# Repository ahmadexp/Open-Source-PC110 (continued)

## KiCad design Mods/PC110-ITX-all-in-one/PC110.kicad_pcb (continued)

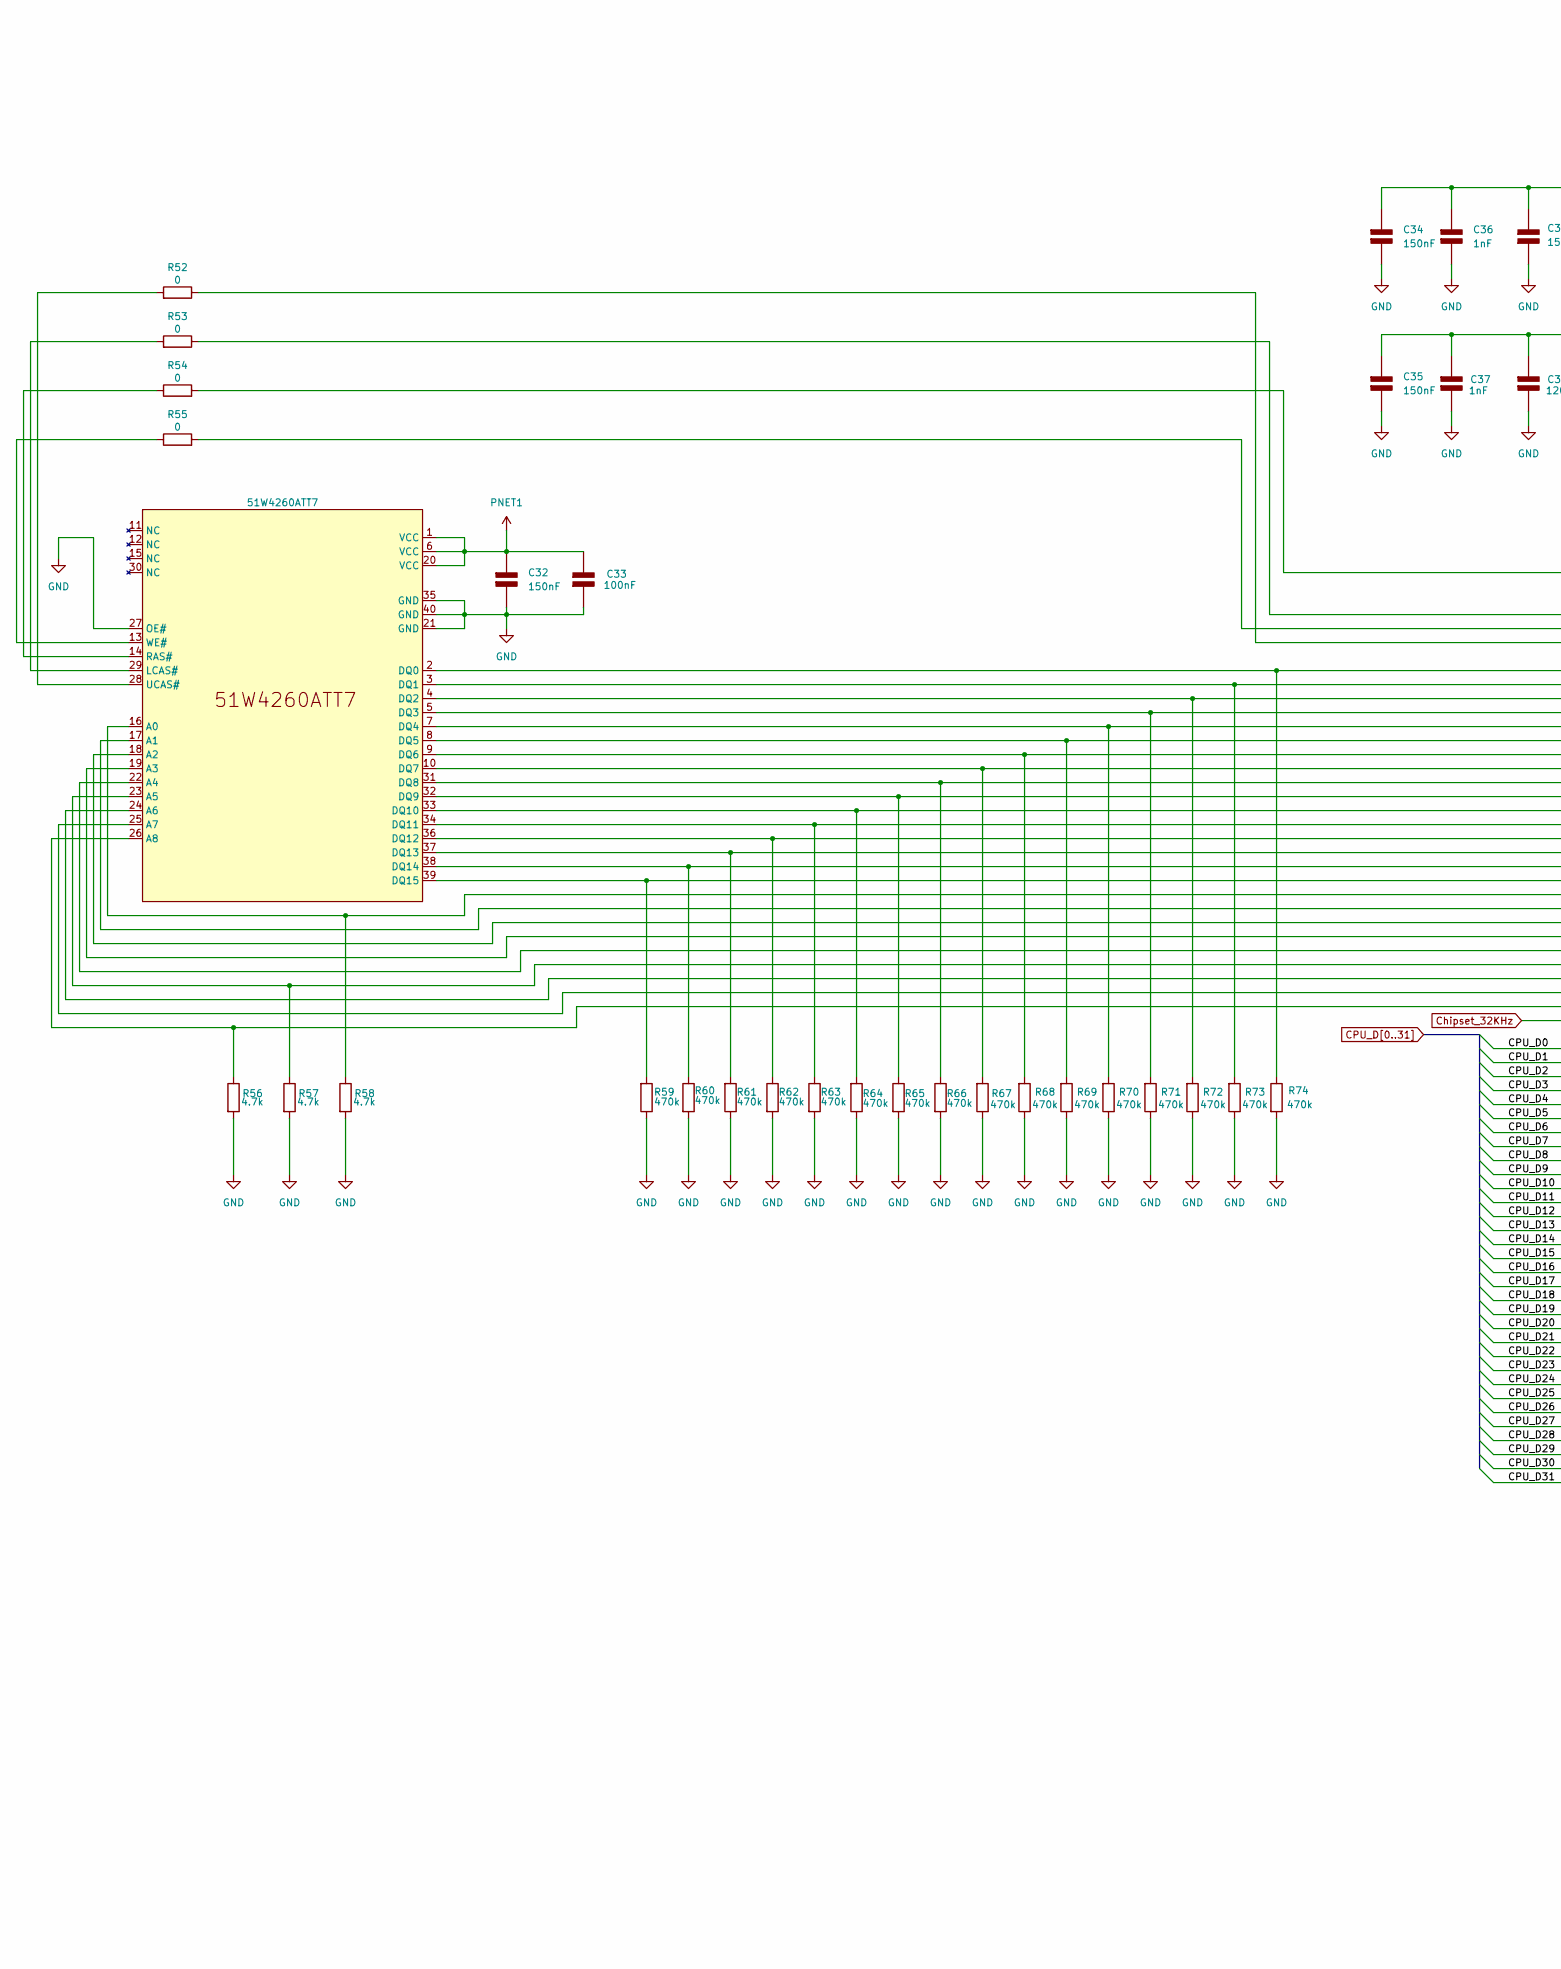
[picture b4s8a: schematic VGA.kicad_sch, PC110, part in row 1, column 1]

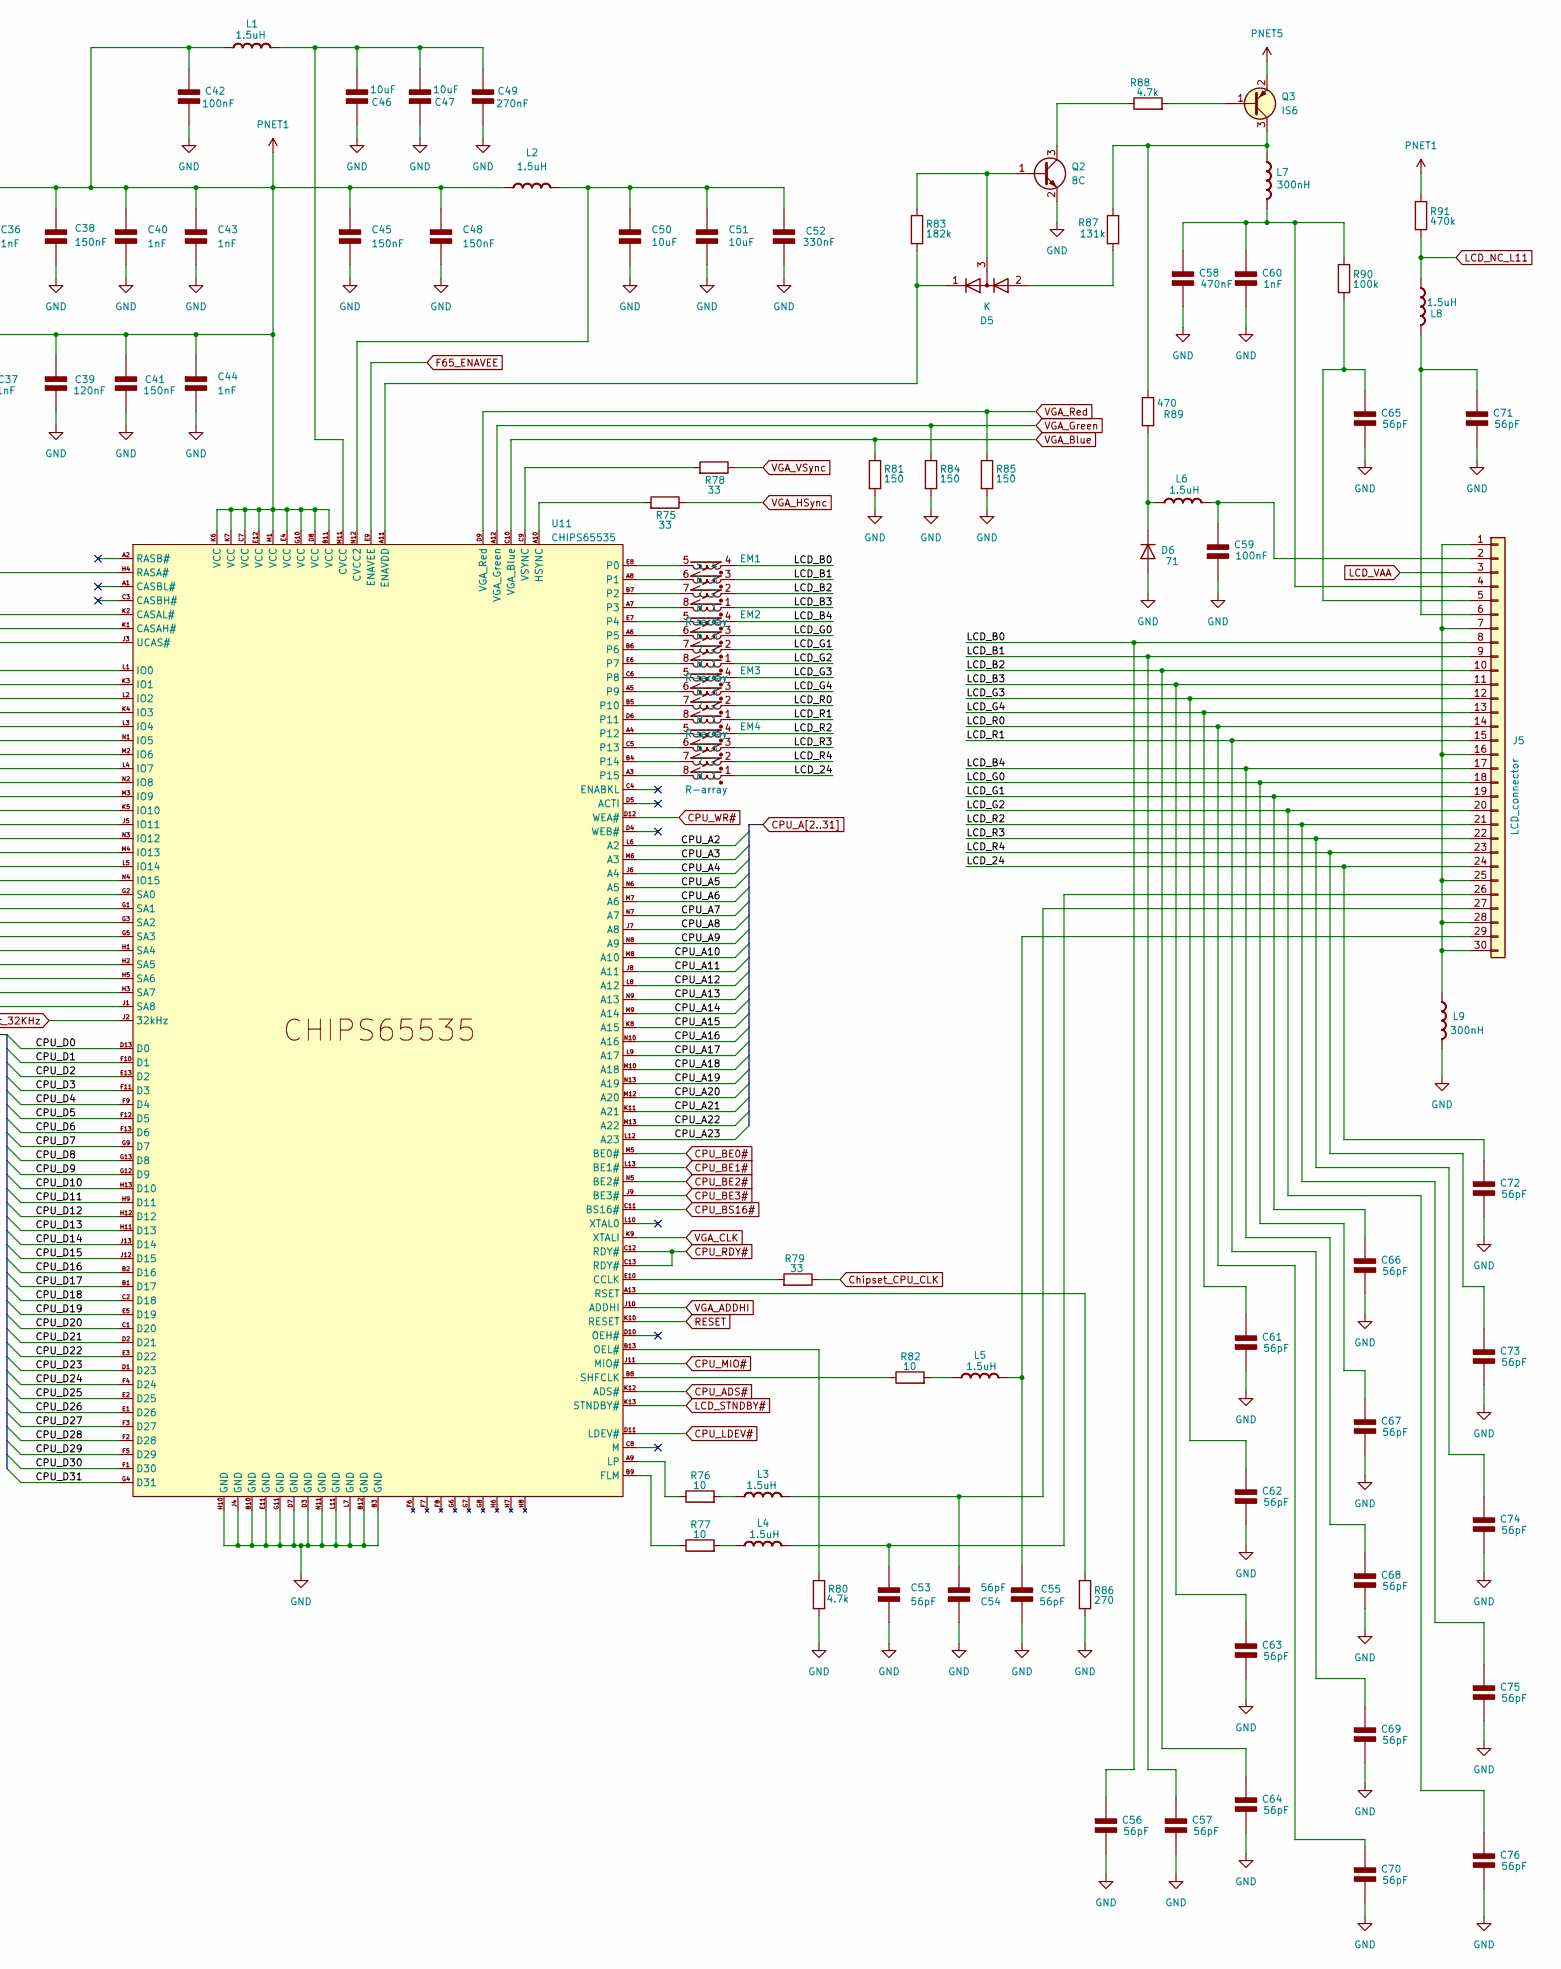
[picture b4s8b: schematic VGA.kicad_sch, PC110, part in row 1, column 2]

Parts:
C32, C34, C35, C38, C41, C45, C48: 150nF; C_0402_1005Metric
C33, C42, C59: 100nF; C_0402_1005Metric
C36, C37, C40, C43, C44, C60: 1nF; C_0402_1005Metric
C39: 120nF; C_0402_1005Metric
C46, C47, C50, C51: 10uF; C_1206_3216Metric
C49: 270nF; C_0603_1608Metric
C52: 330nF; C_0402_1005Metric
C53, C54, C55, C56, C57, C61, C62, C63, C64, C65, C66, C67, C68, C69, C70, C71, C72, C73, C74, C75, C76: 56pF; C_0402_1005Metric
C58: 470nF; C_0603_1608Metric
D5: K; SOT-416L
D6: 71; D_0603_1608Metric
EM1, EM2, EM3, EM4: R-array
J5: LCD_connector
L1, L2, L3, L4, L5, L6, L8: 1.5uH; L_0603_1608Metric
L7, L9: 300nH; L_0805_2012Metric
Q2: 8C; SOT-416
Q3: IS6; SOT-23
R52, R53, R54, R55: 0; R_0402_1005Metric
R56, R57, R58, R80, R88: 4.7k; R_0402_1005Metric
R59, R60, R61, R62, R63, R64, R65, R66, R67, R68, R69, R70, R71, R72, R73, R74, R91: 470k; R_0402_1005Metric
R75, R78, R79: 33; R_0402_1005Metric
R76, R77, R82: 10; R_0402_1005Metric
R81, R84, R85: 150; R_0805_2012Metric
R83: 182k; R_0402_1005Metric
R86: 270; R_0402_1005Metric
R87: 131k; R_0402_1005Metric
R89: 470; R_0402_1005Metric
R90: 100k; R_0402_1005Metric
U10: 51W4260ATT7; GRAMchip
U11: CHIPS65535; BGA-169

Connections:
/VGA Controller/LCD_24: C72.1 (+), EM4.1, J5.24
/VGA Controller/LCD_B0: C56.1 (+), EM1.4, J5.8
/VGA Controller/LCD_B1: C57.1 (+), EM1.3, J5.9
/VGA Controller/LCD_B2: C64.1 (+), EM1.2, J5.10
/VGA Controller/LCD_B3: C63.1 (+), EM1.1, J5.11
/VGA Controller/LCD_B4: C68.1 (+), EM2.4, J5.17
/VGA Controller/LCD_G0: C67.1 (+), EM2.3, J5.18
/VGA Controller/LCD_G1: C66.1 (+), EM2.2, J5.19
/VGA Controller/LCD_G2: C76.1 (+), EM2.1, J5.20
/VGA Controller/LCD_G3: C62.1 (+), EM3.4, J5.12
/VGA Controller/LCD_G4: C61.1 (+), EM3.3, J5.13
/VGA Controller/LCD_R0: C70.1 (+), EM3.2, J5.14
/VGA Controller/LCD_R1: C69.1 (+), EM3.1, J5.15
/VGA Controller/LCD_R2: C75.1 (+), EM4.4, J5.21
/VGA Controller/LCD_R3: C74.1 (+), EM4.3, J5.22
/VGA Controller/LCD_R4: C73.1 (+), EM4.2, J5.23
CPU_A2: U11.L6 (A2); also elsewhere on the board
CPU_A3: U11.M6 (A3); also elsewhere on the board
CPU_A4: U11.J6 (A4); also elsewhere on the board
CPU_A5: U11.N6 (A5); also elsewhere on the board
CPU_A6: U11.M7 (A6); also elsewhere on the board
CPU_A7: U11.N7 (A7); also elsewhere on the board
CPU_A8: U11.J7 (A8); also elsewhere on the board
CPU_A9: U11.N8 (A9); also elsewhere on the board
CPU_A10: U11.M8 (A10); also elsewhere on the board
CPU_A11: U11.J8 (A11); also elsewhere on the board
CPU_A12: U11.L8 (A12); also elsewhere on the board
CPU_A13: U11.N9 (A13); also elsewhere on the board
CPU_A14: U11.M9 (A14); also elsewhere on the board
CPU_A15: U11.K8 (A15); also elsewhere on the board
CPU_A16: U11.N10 (A16); also elsewhere on the board
CPU_A17: U11.L9 (A17); also elsewhere on the board
CPU_A18: U11.M10 (A18); also elsewhere on the board
CPU_A19: U11.N13 (A19); also elsewhere on the board
CPU_A20: U11.M12 (A20); also elsewhere on the board
CPU_A21: U11.K11 (A21); also elsewhere on the board
CPU_A22: U11.M13 (A22); also elsewhere on the board
CPU_A23: U11.L12 (A23); also elsewhere on the board
CPU_ADS#: U11.K12 (ADS#); also elsewhere on the board
CPU_BE0#: U11.M5 (BE0#); also elsewhere on the board
CPU_BE1#: U11.L13 (BE1#); also elsewhere on the board
CPU_BE2#: U11.N5 (BE2#); also elsewhere on the board
CPU_BE3#: U11.J9 (BE3#); also elsewhere on the board
CPU_BS16#: U11.C11 (BS16#); also elsewhere on the board
CPU_D0: U11.D13 (D0); also elsewhere on the board
CPU_D1: U11.F10 (D1); also elsewhere on the board
CPU_D2: U11.E13 (D2); also elsewhere on the board
CPU_D3: U11.F11 (D3); also elsewhere on the board
CPU_D4: U11.F9 (D4); also elsewhere on the board
CPU_D5: U11.F12 (D5); also elsewhere on the board
CPU_D6: U11.F13 (D6); also elsewhere on the board
CPU_D7: U11.G9 (D7); also elsewhere on the board
CPU_D8: U11.G13 (D8); also elsewhere on the board
CPU_D9: U11.G12 (D9); also elsewhere on the board
CPU_D10: U11.H13 (D10); also elsewhere on the board
CPU_D11: U11.H9 (D11); also elsewhere on the board
CPU_D12: U11.H12 (D12); also elsewhere on the board
CPU_D13: U11.H11 (D13); also elsewhere on the board
CPU_D14: U11.J13 (D14); also elsewhere on the board
CPU_D15: U11.J12 (D15); also elsewhere on the board
CPU_D16: U11.B2 (D16); also elsewhere on the board
CPU_D17: U11.B1 (D17); also elsewhere on the board
CPU_D18: U11.C2 (D18); also elsewhere on the board
CPU_D19: U11.E5 (D19); also elsewhere on the board
CPU_D20: U11.C1 (D20); also elsewhere on the board
CPU_D21: U11.D2 (D21); also elsewhere on the board
CPU_D22: U11.E3 (D22); also elsewhere on the board
CPU_D23: U11.D1 (D23); also elsewhere on the board
CPU_D24: U11.F4 (D24); also elsewhere on the board
CPU_D25: U11.E2 (D25); also elsewhere on the board
CPU_D26: U11.E1 (D26); also elsewhere on the board
CPU_D27: U11.F3 (D27); also elsewhere on the board
CPU_D28: U11.F2 (D28); also elsewhere on the board
CPU_D29: U11.F5 (D29); also elsewhere on the board
CPU_D30: U11.F1 (D30); also elsewhere on the board
CPU_D31: U11.G4 (D31); also elsewhere on the board
CPU_LDEV#: U11.D11 (LDEV#); also elsewhere on the board
CPU_MIO#: U11.J11 (MIO#); also elsewhere on the board
CPU_RDY#: U11.C12 (RDY#), U11.C13 (RDY#); also elsewhere on the board
CPU_WR#: U11.D12 (WEA#); also elsewhere on the board
Chipset_32KHz: U11.J2 (32kHz); also elsewhere on the board
Chipset_CPU_CLK: R79.1; also elsewhere on the board
F65_ENAVEE: U11.E9 (ENAVEE); also elsewhere on the board
GND: C32.2 (-), C33.1 (+), C34.2 (-), C35.2 (-), C36.2 (-), C37.2 (-), C38.1 (+), C39.2 (-), C40.2 (-), C41.1 (+), C42.1 (+), C43.2 (-), C44.2 (-), C45.2 (-), C46.1 (+), C47.1 (+), C48.2 (-), C49.2 (-), C50.1 (+), C51.1 (+), C52.2 (-), C53.2 (-), C54.1 (+), C55.1 (+), C56.2 (-), C57.2 (-), C58.2 (-), C59.1 (+), C60.2 (-), C61.2 (-), C62.2 (-), C63.2 (-), C64.2 (-), C65.2 (-), C66.2 (-), C67.2 (-), C68.2 (-), C69.2 (-), C70.2 (-), C71.2 (-), C72.2 (-), C73.2 (-), C74.2 (-), C75.2 (-), C76.2 (-), D6.2 (A), L9.2 (-), Q2.2 (E), R56.2, R57.2, R58.2, R59.1, R60.2, R61.1, R62.2, R63.2, R64.1, R65.2, R66.2, R67.1, R68.1, R69.1, R70.1, R71.1, R72.1, R73.1, R74.2, R80.2, R81.2, R84.2, R85.2, R86.1, U10.21 (GND), U10.27 (OE#), U10.35 (GND), U10.40 (GND), U11.B3 (GND), U11.B10 (GND), U11.B12 (GND), U11.D3 (GND), U11.D7 (GND), U11.E11 (GND), U11.G11 (GND), U11.H10 (GND), U11.J4 (GND), U11.L7 (GND), U11.L11 (GND), U11.N11 (GND); also elsewhere on the board
LCD_NC_L11: L8.2 (-), R91.1; also elsewhere on the board
LCD_STNDBY#: U11.K13 (STNDBY#); also elsewhere on the board
LCD_VAA: J5.3; also elsewhere on the board
unnamed: C46.2 (-), C47.2 (-), C49.1 (+), L1.1 (+), U11.M11 (CVCC)
unnamed: C50.2 (-), C51.2 (-), C52.1 (+), L2.2 (-), U11.N12 (CVCC2)
unnamed: C53.1 (+), J5.26, L4.2 (-)
unnamed: C54.2 (-), J5.27, L3.1 (+)
unnamed: C55.2 (-), J5.29, L5.2 (-)
unnamed: C58.1 (+), C60.1 (+), J5.4, L7.1 (+), R90.2
unnamed: C59.2 (-), J5.2, L6.1 (+)
unnamed: C65.1 (+), J5.5, R90.1
unnamed: C71.1 (+), J5.6, L8.1 (+)
unnamed: D5.2 (A), R87.1
unnamed: D5.1 (K), R83.2, U11.A11 (ENAVDD)
unnamed: D5.3 (common), Q2.1 (B), R83.1
unnamed: D6.1 (K), L6.2 (-), R89.2
unnamed: J5.1, J5.7, J5.16, J5.25, J5.28, J5.30, L9.1 (+)
unnamed: L3.2 (-), R76.2
unnamed: L4.1 (+), R77.2
unnamed: L5.1 (+), R82.2
unnamed: L7.2 (-), Q3.3 (C), R87.2, R89.1
unnamed: Q2.3 (C), R88.1
unnamed: Q3.1 (B), R88.2
unnamed: R58.1, U10.16 (A0), U11.G2 (SA0)
unnamed: U10.17 (A1), U11.G1 (SA1)
unnamed: U10.18 (A2), U11.G3 (SA2)
unnamed: U10.19 (A3), U11.G5 (SA3)
unnamed: U10.22 (A4), U11.H1 (SA4)
unnamed: R57.1, U10.23 (A5), U11.H2 (SA5)
unnamed: U10.24 (A6), U11.H5 (SA6)
unnamed: U10.25 (A7), U11.H3 (SA7)
unnamed: R56.1, U10.26 (A8), U11.J1 (SA8)
unnamed: R74.1, U10.2 (DQ0), U11.L1 (IO0)
unnamed: R73.2, U10.3 (DQ1), U11.K3 (IO1)
unnamed: R72.2, U10.4 (DQ2), U11.L2 (IO2)
unnamed: R71.2, U10.5 (DQ3), U11.K4 (IO3)
unnamed: R70.2, U10.7 (DQ4), U11.L3 (IO4)
unnamed: R69.2, U10.8 (DQ5), U11.N1 (IO5)
unnamed: R68.2, U10.9 (DQ6), U11.M2 (IO6)
unnamed: R67.2, U10.10 (DQ7), U11.L4 (IO7)
unnamed: R66.1, U10.31 (DQ8), U11.N2 (IO8)
unnamed: R65.1, U10.32 (DQ9), U11.M3 (IO9)
unnamed: R64.2, U10.33 (DQ10), U11.K5 (IO10)
unnamed: R63.1, U10.34 (DQ11), U11.J5 (IO11)
unnamed: R62.1, U10.36 (DQ12), U11.N3 (IO12)
unnamed: R61.2, U10.37 (DQ13), U11.M4 (IO13)
unnamed: R60.1, U10.38 (DQ14), U11.L5 (IO14)
unnamed: R59.2, U10.39 (DQ15), U11.N4 (IO15)
unnamed: R53.2, U10.29 (LCAS#)
unnamed: R54.1, U10.14 (RAS#)
unnamed: R52.2, U10.28 (UCAS#)
unnamed: R55.1, U10.13 (WE#)
unnamed: R55.2, U11.K1 (CASAH#)
unnamed: R53.1, U11.K2 (CASAL#)
unnamed: R79.2, U11.E10 (CCLK)
unnamed: R77.1, U11.B9 (FLM)
unnamed: R75.2, U11.A10 (HSYNC)
unnamed: R76.1, U11.A9 (LP)
unnamed: R80.1, U11.B13 (OEL#)
unnamed: EM1.5, U11.E8 (P0)
unnamed: EM1.6, U11.A8 (P1)
unnamed: EM1.7, U11.B7 (P2)
unnamed: EM1.8, U11.A7 (P3)
unnamed: EM2.5, U11.E7 (P4)
unnamed: EM2.6, U11.A6 (P5)
unnamed: EM2.7, U11.B6 (P6)
unnamed: EM2.8, U11.E6 (P7)
unnamed: EM3.5, U11.C6 (P8)
unnamed: EM3.6, U11.A5 (P9)
unnamed: EM3.7, U11.B5 (P10)
unnamed: EM3.8, U11.D6 (P11)
unnamed: EM4.5, U11.A4 (P12)
unnamed: EM4.6, U11.C5 (P13)
unnamed: EM4.7, U11.B4 (P14)
unnamed: EM4.8, U11.A3 (P15)
unnamed: R54.2, U11.H4 (RASA#)
unnamed: R86.2, U11.A13 (RSET)
unnamed: R82.1, U11.B8 (SHFCLK)
unnamed: R52.1, U11.J3 (UCAS#)
unnamed: R78.2, U11.C9 (VSYNC)
PNET1: C32.1 (+), C33.2 (-), C34.1 (+), C35.1 (+), C36.1 (+), C37.1 (+), C38.2 (-), C39.1 (+), C40.1 (+), C41.2 (-), C42.2 (-), C43.1 (+), C44.1 (+), C45.1 (+), C48.1 (+), L1.2 (-), L2.1 (+), R91.2, U10.1 (VCC), U10.6 (VCC), U10.20 (VCC), U11.B11 (VCC), U11.C7 (VCC), U11.D8 (VCC), U11.E4 (VCC), U11.E12 (VCC), U11.G10 (VCC), U11.K6 (VCC), U11.K7 (VCC), U11.M1 (VCC); also elsewhere on the board
PNET5: Q3.2 (E); also elsewhere on the board
RESET: U11.K10 (RESET); also elsewhere on the board
VGA_ADDHI: U11.J10 (ADDHI); also elsewhere on the board
VGA_Blue: R81.1, U11.C10 (VGA_Blue); also elsewhere on the board
VGA_CLK: U11.K9 (XTALI); also elsewhere on the board
VGA_Green: R84.1, U11.A12 (VGA_Green); also elsewhere on the board
VGA_HSync: R75.1; also elsewhere on the board
VGA_Red: R85.1, U11.D9 (VGA_Red); also elsewhere on the board
VGA_VSync: R78.1; also elsewhere on the board

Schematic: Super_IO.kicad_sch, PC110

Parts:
C108, C109, C111: 100nF; C_0402_1005Metric
C110: 1nF; C_0402_1005Metric
C112: 120nF; C_0402_1005Metric
D15, D16: 3D
R137, R139: 100k; R_0402_1005Metric
R138, R141: 470k; R_0402_1005Metric
R140, R142, R145, R147, R148, R149: 1k; R_0402_1005Metric
R143, R144, R146: 2k; R_0402_1005Metric
R150: 10k; R_0402_1005Metric
U26: E4; SOT-353
U27: FDC37C665IR; FDC
U28: EA; SOT-353

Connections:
AEN: U27.44 (AEN); also elsewhere on the board
Chipset_FDC_TC: U27.33 (TC); also elsewhere on the board
FCS_IOCHRDY: U27.98 (IOCHRDY); also elsewhere on the board
FDC_ACK#: R145.1, U27.60 (ACK#); also elsewhere on the board
FDC_AUTOFD#: R142.1, U27.74 (AUTOFD#); also elsewhere on the board
FDC_BUSY: R150.2, U27.59 (BUSY); also elsewhere on the board
FDC_CLK: U27.18 (X1/CLK1); also elsewhere on the board
FDC_CTS1#: U27.80 (CTS1#); also elsewhere on the board
FDC_CTS2#: U27.90 (CTS2#); also elsewhere on the board
FDC_DACK#: R137.1, U27.34 (DACK#); also elsewhere on the board
FDC_DCD1#: U27.83 (DCD1#); also elsewhere on the board
FDC_DCD2#: U27.85 (DCD2#); also elsewhere on the board
FDC_DIR#: U27.5 (DIR#); also elsewhere on the board
FDC_DRATE0: U27.17 (DRATE0); also elsewhere on the board
FDC_DRATE1: U27.16 (DRATE1); also elsewhere on the board
FDC_DS3: U27.95 (A10); also elsewhere on the board
FDC_DSKCHG#: U27.15 (DSKCHG#); also elsewhere on the board
FDC_DSR1: U27.78 (DSR1); also elsewhere on the board
FDC_DSR2#: U27.88 (DSR2#); also elsewhere on the board
FDC_DTR1#: U27.81 (DTR1#); also elsewhere on the board
FDC_DTR2#: U27.91 (DTR2#); also elsewhere on the board
FDC_ERROR#: R147.1, U27.73 (ERROR#); also elsewhere on the board
FDC_FDRQ: U27.50 (FDRQ); also elsewhere on the board
FDC_FINTR: U27.38 (FINTR); also elsewhere on the board
FDC_HDCS0#: U27.23 (HDCS0#); also elsewhere on the board
FDC_HDCS1#: U27.24 (HDCS1#); also elsewhere on the board
FDC_HDSEL#: U27.9 (HDSEL#); also elsewhere on the board
FDC_IDE7: U27.20 (IDED7); also elsewhere on the board
FDC_INDEX#: U27.10 (INDEX#); also elsewhere on the board
FDC_INIT#: R146.1, U27.72 (INIT#); also elsewhere on the board
FDC_IOW: U28.2; also elsewhere on the board
FDC_IRRX_RXD2: R141.1, U27.86 (IRRX/RXD2); also elsewhere on the board
FDC_IRTX_TXD2: U27.87 (IRTX/TXD2); also elsewhere on the board
FDC_MTR2#: R139.1, U27.94 (MTR2#); also elsewhere on the board
FDC_MTR3#: U27.97 (MTR3#); also elsewhere on the board
FDC_PD0: U27.69 (PD0); also elsewhere on the board
FDC_PD1: U27.68 (PD1); also elsewhere on the board
FDC_PD2: U27.67 (PD2); also elsewhere on the board
FDC_PD3: U27.66 (PD3); also elsewhere on the board
FDC_PD4: U27.64 (PD4); also elsewhere on the board
FDC_PD5: U27.63 (PD5); also elsewhere on the board
FDC_PD6: U27.62 (PD6); also elsewhere on the board
FDC_PD7: U27.61 (PD7); also elsewhere on the board
FDC_PE: R148.1, U27.58 (PE); also elsewhere on the board
FDC_RDATA#: U27.14 (RDATA#); also elsewhere on the board
FDC_RI1#: U27.82 (RI1#); also elsewhere on the board
FDC_RI2#: U27.84 (RI2#); also elsewhere on the board
FDC_RTS1#: U27.79 (RTS1#); also elsewhere on the board
FDC_RTS2#: U27.89 (RTS2#); also elsewhere on the board
FDC_RXD1: U27.76 (RXD1); also elsewhere on the board
FDC_SLCT: R149.2, U27.57 (SLCT); also elsewhere on the board
FDC_SLCTIN#: R143.1, U27.71 (SLCTIN#); also elsewhere on the board
FDC_STEP#: U27.6 (STEP#); also elsewhere on the board
FDC_STROBE#: R144.1, U27.75 (STROBE#); also elsewhere on the board
FDC_TRK0#: U27.11 (TRK0#); also elsewhere on the board
FDC_TXD1: U27.77 (TXD1); also elsewhere on the board
FDC_WDATA#: U27.7 (WDATA#); also elsewhere on the board
FDC_WGATE#: U27.8 (WGATE#); also elsewhere on the board
FDC_WRTPRT#: U27.12 (WRTPRT#); also elsewhere on the board
FDD_DRSEL: U27.2 (DS0#); also elsewhere on the board
FDD_MOTEN: U27.100 (MTR0#); also elsewhere on the board
GND: C108.2 (-), C109.2 (-), C110.2, C111.2 (-), C112.2, R138.2, U26.3 (GND), U27.4 (VSS), U27.45 (VSS), U27.65 (VSS), U27.93 (VSS), U28.3 (GND); also elsewhere on the board
IOCS16#: R140.2, U27.25 (IOCS16#); also elsewhere on the board
IOR#: U27.42 (IOR#); also elsewhere on the board
IOW#: U26.2; also elsewhere on the board
IRQ3: U27.35 (IRQ3); also elsewhere on the board
IRQ4: U27.36 (IRQ4); also elsewhere on the board
IRQ5: U27.92 (DRV2/ADRx/PINTR2); also elsewhere on the board
IRQ7: U27.37 (PINTR); also elsewhere on the board
unnamed: D15.2 (K), R142.2, R143.2, R144.2, R145.2
unnamed: D16.2 (K), R146.2, R147.2, R148.2, R149.1, R150.1
unnamed: U26.1, U28.4
unnamed: U26.4, U27.43 (IOW#)
PNET1: C109.1 (+), C110.1, R137.2, R139.2, U26.5 (VCC), U27.13 (VCC), U27.70 (VCC), U28.5 (VCC); also elsewhere on the board
PNET5: C108.1 (+), C111.1 (+), C112.1, D15.1 (A), D15.3 (A), D16.1 (A), D16.3 (A), R141.2, U27.96 (VIO); also elsewhere on the board
PNET7: R140.1; also elsewhere on the board
PWRGD: R138.1, U27.56 (PWRGD); also elsewhere on the board
RESET: U27.55 (RESET); also elsewhere on the board
SA0: U27.26 (A0); also elsewhere on the board
SA1: U27.27 (A1); also elsewhere on the board
SA2: U27.28 (A2); also elsewhere on the board
SA3: U27.29 (A3); also elsewhere on the board
SA4: U27.30 (A4); also elsewhere on the board
SA5: U27.31 (A5); also elsewhere on the board
SA6: U27.32 (A6); also elsewhere on the board
SA7: U27.39 (A7); also elsewhere on the board
SA8: U27.40 (A8); also elsewhere on the board
SA9: U27.41 (A9); also elsewhere on the board
SD0: U27.46 (D0); also elsewhere on the board
SD1: U27.47 (D1); also elsewhere on the board
SD2: U27.48 (D2); also elsewhere on the board
SD3: U27.49 (D3); also elsewhere on the board
SD4: U27.51 (D4); also elsewhere on the board
SD5: U27.52 (D5); also elsewhere on the board
SD6: U27.53 (D6); also elsewhere on the board
SD7: U27.54 (D7); also elsewhere on the board

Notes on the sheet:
Device_Address_BUS
Device_Data_BUS

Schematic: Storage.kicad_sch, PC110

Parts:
C225, C228, C240, C241: 150nF; C_0402_1005Metric
C226, C227, C231, C232, C233, C234, C238, C244: 100nF; C_0402_1005Metric
C229: 180pF; C_0402_1005Metric
C230: 220pF; C_0402_1005Metric
C235: 1.5uF; C_0805_2012Metric
C236: 10nF; C_0603_1608Metric
C237: 100nF; C_0603_1608Metric
C239: 150nF; C_0603_1608Metric
C242, C243: 100pF; C_0402_1005Metric
F2: 0.5A; Fuse_1206_3216Metric
J13: CF-card
Q38: BH RT; SOT-89-3
R330, R331, R332, R333, R334, R335, R336, R337: 4.7k; R_0402_1005Metric
R338: DNP; R_0805_2012Metric
R339: 0; R_0805_2012Metric
R340, R342, R345, R348: 470k; R_0402_1005Metric
R341, R359: DNP; R_0402_1005Metric; not fitted
R343, R350, R351, R354, R355: DNP; R_0402_1005Metric
R344, R358: 10k; R_0402_1005Metric
R346, R347, R349, R353: 0; R_0402_1005Metric
R352: 22k; R_0402_1005Metric
R356, R357: 2k; R_0402_1005Metric
R360: 1.5k; R_0402_1005Metric
U61: SN74LV32; TSSOP-14_4.4x5mm_P0.65mm
U62: SN74LV08; TSSOP-14_4.4x5mm_P0.65mm
U63: SC414281PU4; QFN-100
U64: E4; SOT-353
U65: AT29LV512-12TU; Flash-32
U66: SDLB-4; SanDisk

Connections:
CF_CD1_Pluto: J13.2 (CD1#), R342.2; also elsewhere on the board
CF_CD2_Pluto: J13.49 (CD2#), R340.1; also elsewhere on the board
FCS_BVD1: J13.42 (BVD1), U63.50 (BVD1)
FCS_BVD2: J13.40 (BVD2), U63.49 (BVD2)
FCS_IOCHRDY: J13.34 (IOCHRDY), U63.47 (WAIT); also elsewhere on the board
FCS_RESET: J13.32 (RESET), R341.1, U63.36 (RESET); also elsewhere on the board
FDC_HDCS0#: R347.2, U62.1; also elsewhere on the board
FDC_HDCS1#: R346.2, U62.2; also elsewhere on the board
FDC_IDE7: J13.11 (SD7), R352.2, U63.13 (HD7); also elsewhere on the board
GND: C225.2 (-), C226.2, C227.2 (-), C228.2, C230.1, C231.2, C232.2, C233.1, C234.1, C235.1, C236.2, C237.2, C239.1, C242.1, C243.1, J13.1 (GND), J13.15 (GND), J13.16 (GND), J13.17 (GND), J13.19 (GND), J13.21 (GND), J13.23 (GND), J13.27 (GND), J13.29 (GND), J13.31 (GND), J13.33 (GND), J13.50 (GND), R341.2, R343.1, R359.1, U61.7 (GND), U61.9, U61.10, U61.12, U61.13, U62.4, U62.5, U62.7 (GND), U62.9, U62.10, U62.12, U62.13, U63.10 (GND), U63.20 (GND), U63.23 (CSEL), U63.24 (SA10), U63.25 (SA9), U63.26 (SA8), U63.27 (SA7), U63.28 (SA6), U63.29 (SA5), U63.30 (SA4), U63.31 (SA3), U63.32 (GND), U63.40 (OE), U63.44 (GND), U63.51 (WPROTCT), U63.61 (GND), U63.70 (GND), U63.82 (GND), U63.94 (GND), U64.2, U64.3 (GND), U65.24 (GND), U66.3 (GND), U66.6 (GND), U66.8 (GND), U66.12 (GND), U66.15 (GND), U66.16 (GND), U66.18 (GND), U66.19 (GND); also elsewhere on the board
IOCS16#: J13.47 (IOCS16#), U63.52 (IO16); also elsewhere on the board
IOR#: R349.2, R350.1, U61.1; also elsewhere on the board
IOW#: R351.2, R353.2, U61.4; also elsewhere on the board
IRQ14: J13.24 (IRQ14), R344.1, U63.46 (RDY); also elsewhere on the board
unnamed: C225.1 (+), C227.1 (+), F2.2, J13.25 (VCC), J13.26 (VCC)
unnamed: C229.1, C230.2
unnamed: C229.2, R357.2
unnamed: J13.13 (CE1#), R347.1, R348.1, U63.37 (CE1)
unnamed: J13.14 (CE2#), R345.1, R346.1, U63.39 (CE2)
unnamed: J13.28 (CSEL#), R343.2
unnamed: J13.18 (IOR#), R349.1, R354.2
unnamed: J13.20 (IOW#), R353.1, R355.2
unnamed: Q38.1 (B), R360.1
unnamed: C236.1, Q38.2 (C), U66.28 (VCC)
unnamed: R360.2, U64.4
unnamed: U61.2, U61.5, U62.3
unnamed: U63.55 (CS), U66.7 (CS)
unnamed: R356.2, R357.1, U63.12 (C_EXT)
unnamed: U63.66 (IO0), U64.1
unnamed: R350.2, R354.1, U61.3, U63.42 (IORD)
unnamed: R351.1, R355.1, U61.6, U63.43 (IOWR)
unnamed: U63.74 (MA0), U65.20 (MA0)
unnamed: U63.75 (MA1), U65.19 (MA1)
unnamed: U63.76 (MA2), U65.18 (MA2)
unnamed: U63.77 (MA3), U65.17 (MA3)
unnamed: U63.78 (MA4), U65.16 (MA4)
unnamed: U63.79 (MA5), U65.15 (MA5)
unnamed: U63.80 (MA6), U65.14 (MA6)
unnamed: U63.81 (MA7), U65.13 (MA7)
unnamed: U63.83 (MA8), U65.3 (MA8)
unnamed: U63.84 (MA9), U65.2 (MA9)
unnamed: U63.85 (MA10), U65.31 (MA10)
unnamed: U63.86 (MA11), U65.1 (MA11)
unnamed: U63.87 (MA12), U65.12 (MA12)
unnamed: U63.89 (MA13), U65.4 (MA13)
unnamed: U63.90 (MA14), U65.5 (MA14)
unnamed: U63.91 (MA15), U65.11 (MA15)
unnamed: U63.92 (MD0), U65.21 (MD0)
unnamed: U63.93 (MD1), U65.22 (MD1)
unnamed: U63.95 (MD2), U65.23 (MD2)
unnamed: U63.96 (MD3), U65.25 (MD3)
unnamed: U63.97 (MD4), U65.26 (MD4)
unnamed: U63.98 (MD5), U65.27 (MD5)
unnamed: U63.99 (MD6), U65.28 (MD6)
unnamed: U63.100 (MD7), U65.29 (MD7)
unnamed: U63.57 (PD), U66.4 (PD)
unnamed: R356.1, U63.11 (RC_IN)
unnamed: U63.71 (ROMCEL0), U65.30 (ROMCEL0#)
unnamed: U63.72 (ROMOEL), U65.32 (ROMOEL#)
unnamed: R358.1, R359.2, U63.73 (ROMWEL), U65.7 (ROMWEL#)
unnamed: U63.53 (SCLK1), U66.5 (SCLK1)
unnamed: U63.59 (SI0), U66.1 (SI0)
unnamed: U63.58 (SI1), U66.2 (SI1)
unnamed: U63.62 (SO0), U66.13 (SO0)
unnamed: U63.60 (SO1), U66.17 (SO1)
unnamed: C237.1, C239.2, U66.10 (Cext1)
unnamed: C238.1, U66.20 (Cext2)
unnamed: C241.1, U66.21 (Cext3)
unnamed: C240.1, C242.2, U66.22 (Cext4)
unnamed: C238.2, C243.2, U66.23 (Cext5)
unnamed: C244.1, U66.24 (Cext6)
unnamed: C240.2, U66.25 (Cext7)
unnamed: C241.2, U66.26 (Cext8)
unnamed: C244.2, U66.27 (Cext9)
PNET1: R338.1, R340.2, R342.1; also elsewhere on the board
PNET7: R330.2, R331.2, R332.2, R333.2, R334.2, R335.2, R336.2, R337.2, R339.1, R344.2; also elsewhere on the board
PNET12: C226.1, C228.1, C231.1, C232.1, C233.2, C234.2, C235.2, F2.1, Q38.3 (E), R338.2, R339.2, R345.2, R348.2, R352.1, R358.2, U61.14 (VCC), U62.14 (VCC), U63.5 (VCC), U63.15 (VCC), U63.38 (VCC), U63.56 (VCC), U63.65 (VCC), U63.88 (VCC), U64.5 (VCC), U65.8 (VCC)
SA0: J13.39 (SA0), U63.35 (SA0); also elsewhere on the board
SA1: J13.37 (SA1), U63.34 (SA1); also elsewhere on the board
SA2: J13.35 (SA2), U63.33 (SA2); also elsewhere on the board
SD0: J13.41 (SD0), R330.1, U63.22 (HD0); also elsewhere on the board
SD1: J13.43 (SD1), R331.1, U63.21 (HD1); also elsewhere on the board
SD2: J13.45 (SD2), R332.1, U63.19 (HD2); also elsewhere on the board
SD3: J13.3 (SD3), R333.1, U63.18 (HD3); also elsewhere on the board
SD4: J13.5 (SD4), R334.1, U63.17 (HD4); also elsewhere on the board
SD5: J13.7 (SD5), R335.1, U63.16 (HD5); also elsewhere on the board
SD6: J13.9 (SD6), R336.1, U63.14 (HD6); also elsewhere on the board
SD7: R337.1; also elsewhere on the board
SD8: J13.44 (SD8), U63.9 (HD8); also elsewhere on the board
SD9: J13.46 (SD9), U63.8 (HD9); also elsewhere on the board
SD10: J13.48 (SD10), U63.7 (HD10); also elsewhere on the board
SD11: J13.4 (SD11), U63.6 (HD11); also elsewhere on the board
SD12: J13.6 (SD12), U63.4 (HD12); also elsewhere on the board
SD13: J13.8 (SD13), U63.3 (HD13); also elsewhere on the board
SD14: J13.10 (SD14), U63.2 (HD14); also elsewhere on the board
SD15: J13.12 (SD15), U63.1 (HD15); also elsewhere on the board

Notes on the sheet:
Device_Data_BUS
Device_Address_BUS
